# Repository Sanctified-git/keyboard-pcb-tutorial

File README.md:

# keyboard-pcb-tutorial
Practicing ai03's PCB design guide

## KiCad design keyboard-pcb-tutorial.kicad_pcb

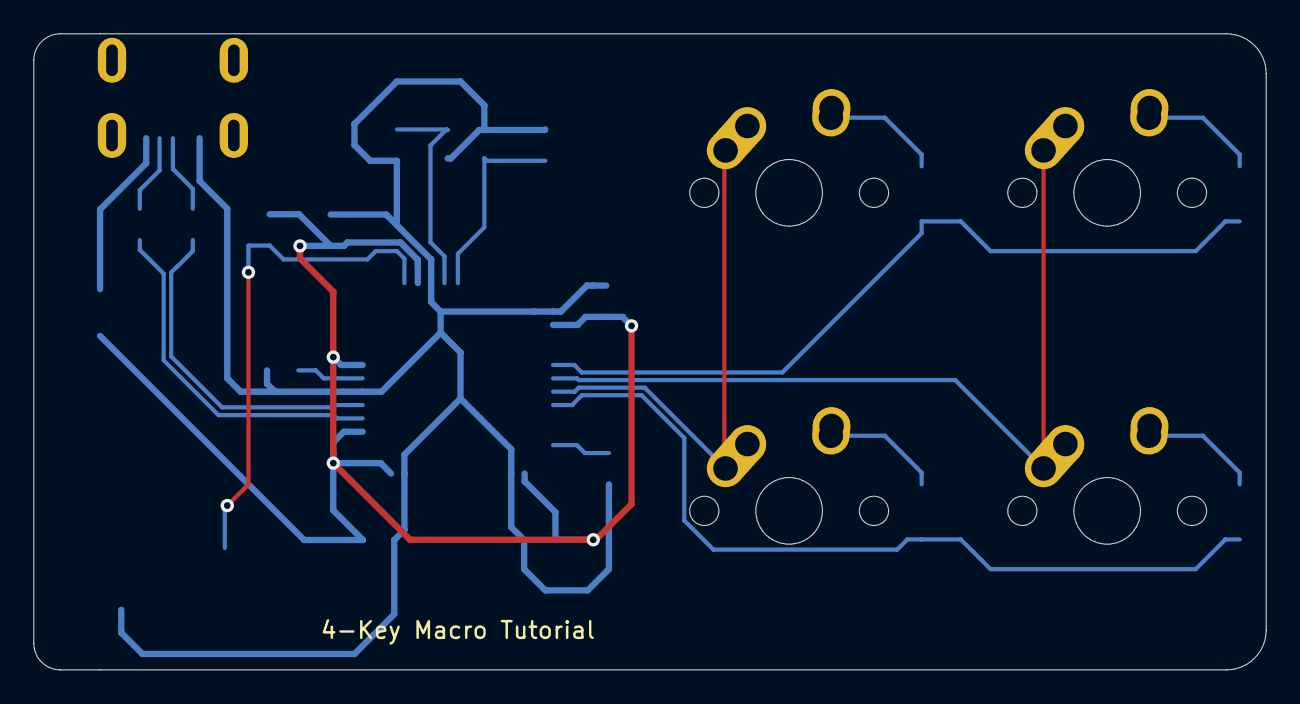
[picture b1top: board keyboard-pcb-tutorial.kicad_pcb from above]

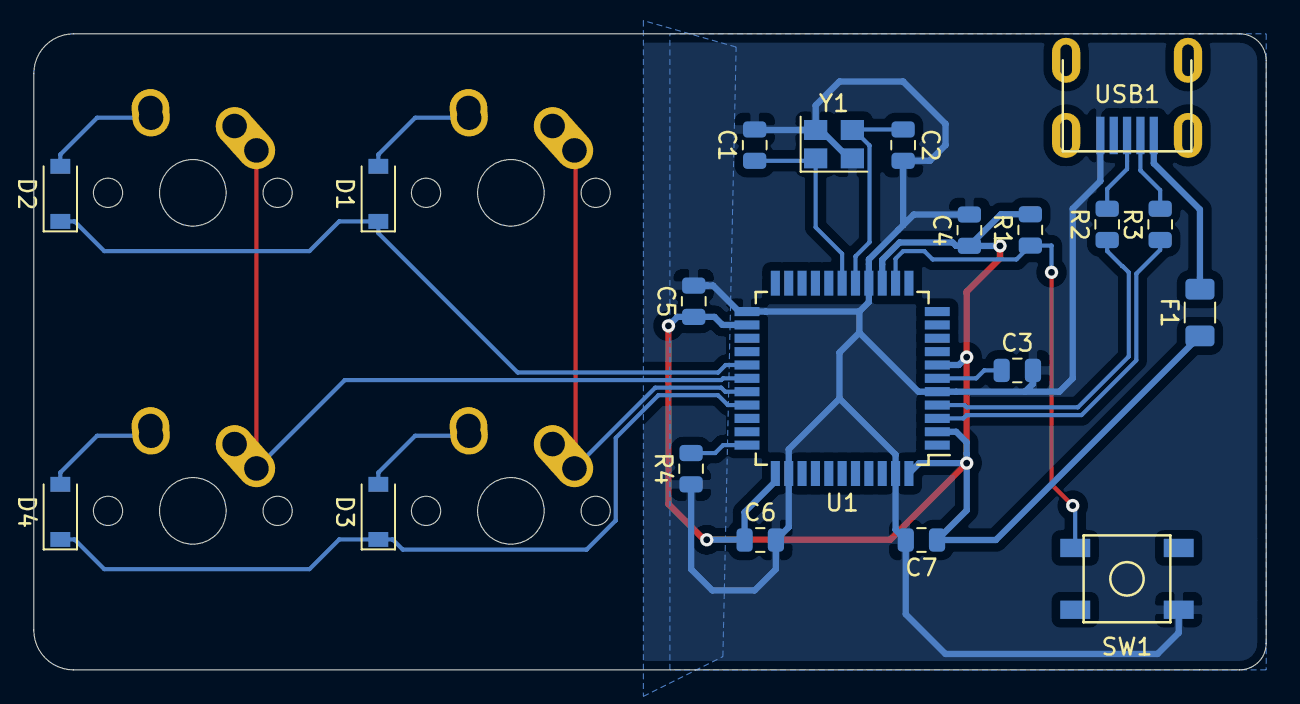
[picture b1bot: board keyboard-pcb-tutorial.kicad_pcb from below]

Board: 2 copper layers, 73.8 x 38.1 mm, 24 parts (20 on the bottom side), 20 nets.

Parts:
C1, C2: 22pF; C_0805_2012Metric
C3: 1uF; C_0805_2012Metric
C4, C5, C6: 0.1uF; C_0805_2012Metric
C7: 10uF; C_0805_2012Metric
D1, D2, D3, D4: SOD-123; D_SOD-123
F1: 500mA; Fuse_1206_3216Metric
MX1, MX2, MX3, MX4: MX-NoLED; MX-1U-NoLED
R1, R4: 10k; R_0805_2012Metric
R2, R3: 22; R_0805_2012Metric
SW1: SW_Push; SKQG-1155865
U1: ATmega32U4-AU; TQFP-44_10x10mm_P0.8mm
USB1: Molex-0548190589
Y1: 16MHz; Crystal_SMD_3225-4Pin_3.2x2.5mm

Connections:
+5V: C4.1, C5.1, C6.1, C7.1, F1.1, R1.2, U1.2, U1.7, U1.14, U1.24, U1.34, U1.44
COL0: MX1.1, MX3.1, U1.29
COL1: MX2.1, MX4.1, U1.28
D+: R2.2, USB1.3
D-: R3.2, USB1.4
GND: C1.2, C2.2, C3.2, C4.2, C5.2, C6.2, C7.2, R4.1, SW1.1, U1.5, U1.15, U1.23, U1.35, U1.43, USB1.1, Y1.2, Y1.4
unnamed: C1.1, U1.17, Y1.1
unnamed: C2.1, U1.16, Y1.3
unnamed: C3.1, U1.6
unnamed: D1.2, MX1.2
unnamed: D2.2, MX2.2
unnamed: D3.2, MX3.2
unnamed: D4.2, MX4.2
unnamed: R1.1, SW1.2, U1.13
unnamed: R2.1, U1.4
unnamed: R3.1, U1.3
unnamed: R4.2, U1.33
ROW0: D1.1, D2.1, U1.27
ROW1: D3.1, D4.1, U1.30
VCC: F1.2, USB1.5

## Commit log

2021-02-01 Initalize kicad project
2021-02-01 Add Required Submodules
2021-02-01 Connected MCU pins
2021-02-02 Added switch matrix schematic
2021-02-02 Added footprints
2021-02-02 added basic pcb layout
2021-02-02 Finished routing
